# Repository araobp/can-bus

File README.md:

# IoT with CAN bus

Printed circuit design for CAN node

(I have not tested the printed circuit board yet, because I have been too busy in other priority works)

## Motivation

I want to develop very cheap and low power sensor/actuator network with electronic parts sold in [Akizuki-Denshi](http://akizukidenshi.com/catalog/default.aspx), Tokyo.

Most of parts I use are DIP.

## Architecture

### Basic concept

I pursue seamless communications between CAN-bus and MQTT-bus:

## Specification

The CAN node consists of one base board and one expansion board.

See this page for expansion boards: [EXPANSION BOARDS](./EXPANSION_BOARDS.md).

### CAN node base board

|Parameter           |Value                       |Note
|--------------------|----------------------------|---------------------------|
|PIC16F1 MCU clock   |32MHz(Internal OSC 8MHz * 4 PLL)                        |
|UART baud rate      |9600bps (fixed)             |Full-duplex wire-rate is not supported|
|SPI clock           |2MHz (fixed)                |                           |
|CAN speed           |Max. 250kHz (default 125kHz)|                           |
|Oscillator for CAN controller|8MHz (ceramic)     |Murata Ceralock            |
|Expansion board     |8 pins connected to PIC MCU |                           |

#### Circuit

#### PCB

#### BOM

|Part                      |Akizuki-denshi URL |Price in Yen |Quantity|
|--------------------------|-------------------|-------------|--------|
|Microchip PIC16F1825-I/P  |http://akizukidenshi.com/catalog/g/gI-10656/|150|1|
|Microchip PIC16F18326-I/P |http://akizukidenshi.com/catalog/g/gI-11886/|130|1|
|Microchip MCP2515         |http://akizukidenshi.com/catalog/g/gI-12030/|160|1|
|Microchip MCP2561         |http://akizukidenshi.com/catalog/g/gI-12483/|90|1|
|Murata Ceralock 8MHz      |http://akizukidenshi.com/catalog/g/gP-00153/|35|1|
|Regiter 51k ohm           |http://akizukidenshi.com/catalog/g/gR-25513/|1|1|
|Register 10k ohm          |http://akizukidenshi.com/catalog/g/gR-25103/|1|1|
|Register 120 ohm          |http://akizukidenshi.com/catalog/g/gR-25121/|1|1|
|Murata capacitor 0.1 micro F|http://akizukidenshi.com/catalog/g/gP-00090/|10|3|
|Diode 1A                  |http://akizukidenshi.com/catalog/g/gI-08332/|10|1|
|Toshiba TA48M05F (w/ capacitors)|http://akizukidenshi.com/catalog/g/gI-00451/|100|1|
|Polyswitch 250mA          |http://akizukidenshi.com/catalog/g/gP-01354|30|2|
|LED 3mm red               |http://akizukidenshi.com/catalog/g/gI-04780/|20|1|
|Tactile switch            |http://akizukidenshi.com/catalog/g/gP-08216/|20|1|
|IC sockets 14pins         |http://akizukidenshi.com/catalog/g/gP-00006/|10|1|
|IC sockets 18pins         |http://akizukidenshi.com/catalog/g/gP-00008/|10|1|
|IC sockets 8pins          |http://akizukidenshi.com/catalog/g/gP-00017/|10|1|
|Pin socket 6pins          |http://akizukidenshi.com/catalog/g/gC-03784/|20|1|
|Pin socket 4pins          |http://akizukidenshi.com/catalog/g/gC-10099/|20|2|
|Pin header L shape        |http://akizukidenshi.com/catalog/g/gC-01627/|50|1|
|Phenix Contact terminal block 2P|http://akizukidenshi.com/catalog/g/gP-08369/|20|1|

### CAN Standard Identifier format

This implementation supports CAN Standard Frame only (does not support Extended Frame). For home networking, 11bit Standard Identifier suffices.

=> [FORMAT](./doc/FORMAT.md)

### "CAN adapter to UART" command list

This implementation supports CAN adapter functionality for PC and Android.

```
/// UART2CAN HELP (version 0.11  March 19, 2018) ///
[Set standard identifier] @i<standard identifier>
[Set output mode] {debug: @vd, verbose: @vv, normal: @vn}
[Enable operation mode] {loopback: @ol, normal: @on}
     with SID: @ols or @ons
[Set mask] @m<n><mask(SID10 ~ SID0)>
[Set filter] @f<n><filter(SID10 ~ SID0)>
[Set baud rate] @b<bpr>
[Abort all pending transmissions] @a
[Dump masks and filters] @F
[Dump registers] @D
[Send message] <message>
[Send message beginning with '@' character] @<@message>
[Receive message] <message> will be output
[Show this help]: @h
```
For example, to receive messages with SID 5, 10 and 15, set masks and filters to the CAN adapter as follows:

```
@m02047  --> RXM0 0b11111111111
@f05     --> RXF0 0b00000000101 (SID 5 message to RXB0)
@f110    --> RXF1 0b00000001010 (SID 10 message to RXB0)
@m12047  --> RXM1 0b11111111111
@f215    --> RXF2 0b00000001111 (SID 15 message to RXB1)
```

---
## Development environment

- Microchip [MPLAB-X IDE](http://www.microchip.com/mplab/mplab-x-ide) with MCC plugin.
- [FreeCAD](https://www.freecadweb.org/)
- [KiCAD](http://kicad.org/)
- [3D printer BIQU Magician](https://www.biqu.equipment/collections/3d-printer/products/biqu-magician-3d-printer-new-diy-kit-mini-kossel-delta-printing)
- [RaspberryPi](https://www.raspberrypi.org/)

---

## Development plan and progress

### M1 (completed on March 17, 2018)

- Purchased CAN adaptors from Amazon.
- Evaluate CAN ==> [EVALUATION](./doc/EVALUATION.md).
- Developed my original ASCII-based protocol over serial for MCP2515. The protocol is mainly for evaluating MCP2515.

At first, I use [this universal board](http://akizukidenshi.com/catalog/g/gP-08241/) to make a prototype of the CAN adaptor:

I have finished the first prototype (Marth 25-27, 2018). I have made three boards, and it took eight hours.

### M2 (completed on April 1, 2018)

3D printed enclosure for CAN node

- Purchase three pairs of MCP2515 and MCP2561 in Akihabara.
- Develop my original CAN adaptor board.
- Develop [CAN-MQTT gateway](./gateway/gateway.js) on RasPi ~~and OpenWrt~~.
- Develop [a 3D-printed DIN rail enclosure](./cad/adapter_to_uart.stl) for the board by using [FreeCAD](https://www.freecadweb.org/).
- ~~Mount all of them on DIN rail (incl. RasPi).~~
- ~~Add [SLCAN](https://elixir.bootlin.com/linux/v3.4/source/drivers/net/can/slcan.c) that is ASCII-based protocol for SocketCAN.~~

### M3

- Evaluate [PIC16F18326](http://akizukidenshi.com/catalog/g/gI-11886/) that is cheaper than PIC16F1825 and supports two MSSPs.
- Use KiCAD to redesign the circuit for PIC16F18326.
- Adopt moduler architecture: base board and sensor/actuator building blocks.
- Support sensors and actuators: doppler sensor, CdS, servo motor etc.

---
## Reference

### Datasheet (Microchip/NXP/Murata)

#### Microchip
- [PIC16F1825](http://ww1.microchip.com/downloads/en/DeviceDoc/41440A.pdf)
- [MCP2515](http://ww1.microchip.com/downloads/en/DeviceDoc/21801d.pdf)
- [MCP2561](http://ww1.microchip.com/downloads/en/DeviceDoc/20005167C.pdf)
- [MCP2515DM-BM](http://www.microchip.com/Developmenttools/ProductDetails.aspx?PartNO=MCP2515DM-BM)

#### NXP
- [TJA1050](https://www.nxp.com/docs/en/data-sheet/TJA1050.pdf)

#### Murata
- [Ceralock](https://www.murata.com/~/media/webrenewal/support/library/catalog/products/timingdevice/ceralock/p17e.ashx)

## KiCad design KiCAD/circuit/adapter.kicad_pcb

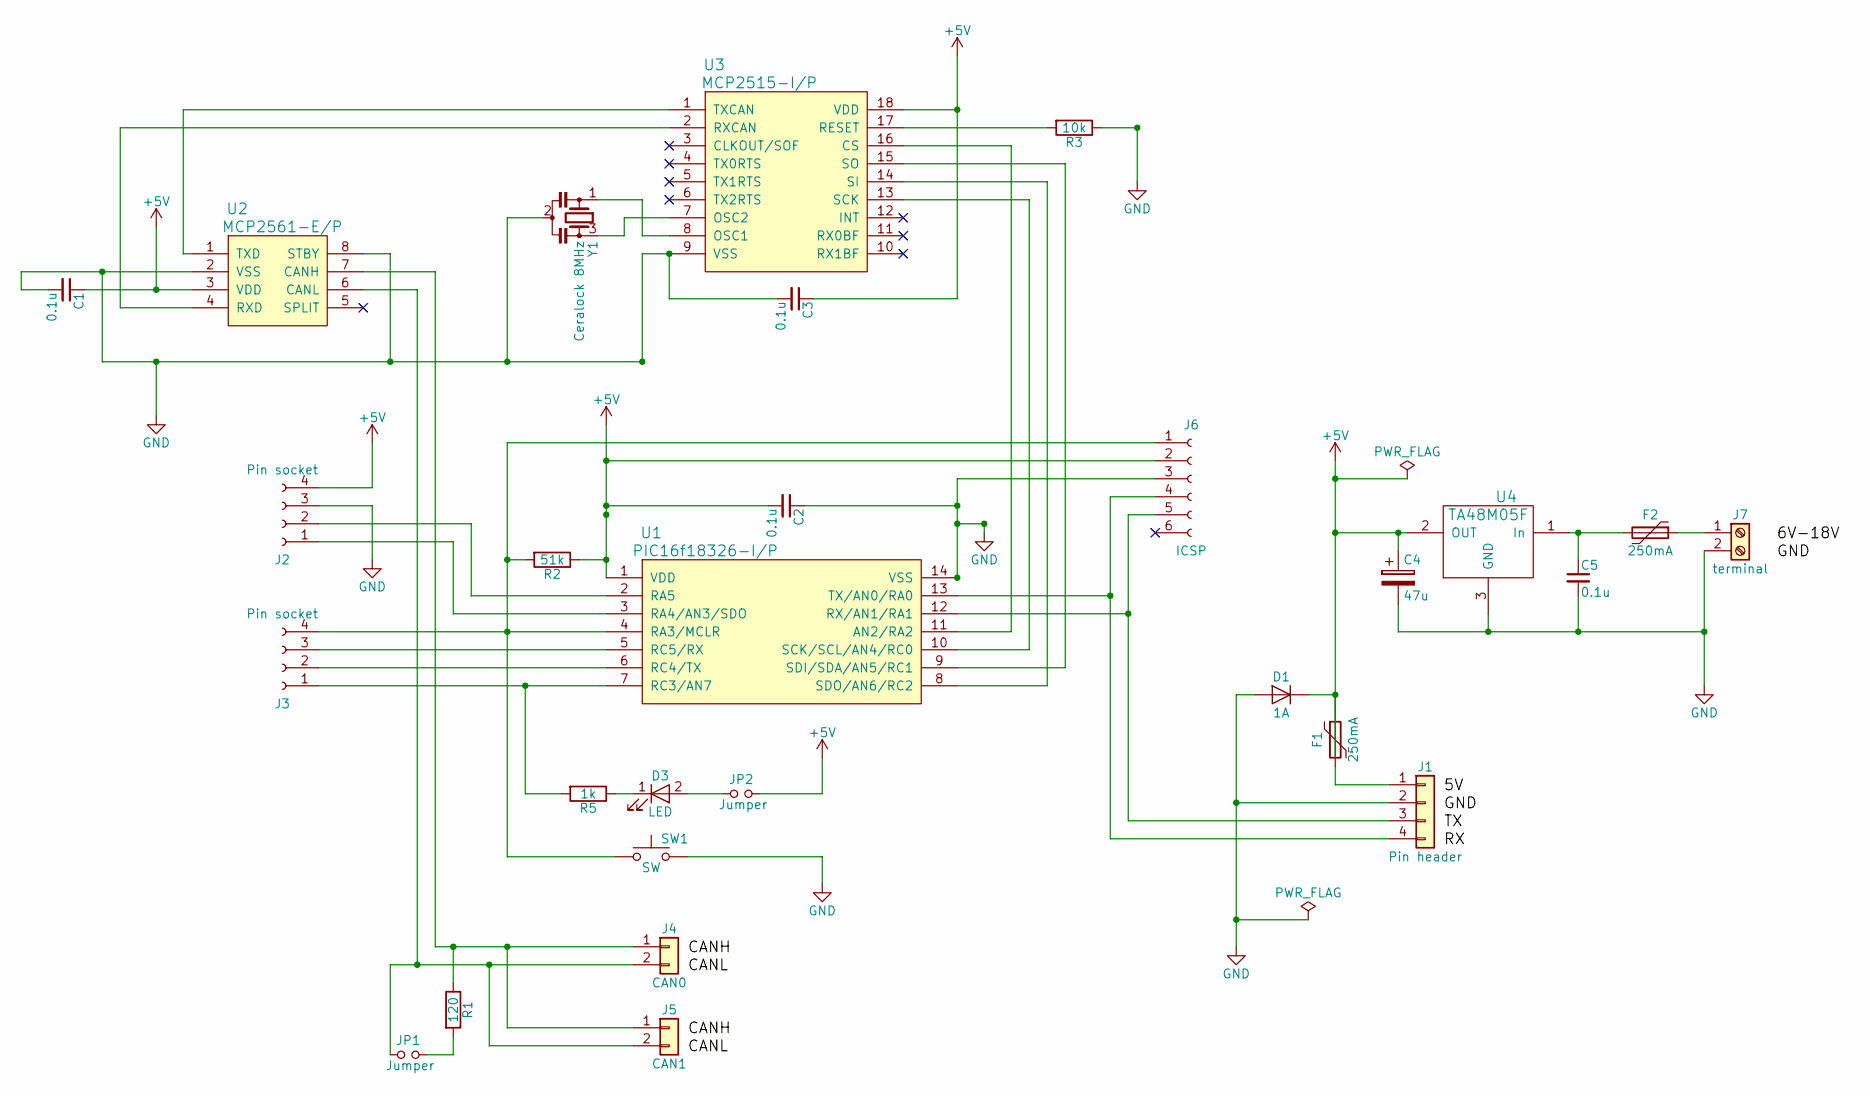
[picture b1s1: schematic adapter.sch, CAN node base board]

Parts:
C1, C2, C3, C5: 0.1u; Capacitor_2.54mm
C4: 47u; Capacitor_2.54mm
D1: 1A; Diode
D3: LED; Led
F1, F2: 250mA; Polyswitch_Tyco
J1: Pin header; PinHeader_1x4_L_Shape
J2, J3: Pin socket; PinSocket_1x4
J4: CAN0; PinHeader_1x2_L_Shape
J5: CAN1; PinHeader_1x2_L_Shape
J6: ICSP; PinSocket_1x6
J7: terminal; Terminal_PhoenixContact_2P
JP1, JP2: Jumper; Jumper_1x2
R1: 120; Resistor_FaithfulLink_CF25
R2: 51k; Resistor_FaithfulLink_CF25
R3: 10k; Resistor_FaithfulLink_CF25
R5: 1k; Resistor_FaithfulLink_CF25
SW1: SW; TactileSwitch
U1: PIC16f18326-I/P; IC_socket_14pins
U2: MCP2561-E/P; IC_Socket_8pins
U3: MCP2515-I/P; IC_socket_18pins
U4: TA48M05F
Y1: Ceralock 8MHz; Ceralock_Murata

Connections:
+5V: C1.1, C2.2, C3.1, C4.1, D1.1 (K), F1.1, J2.4, J6.2, JP2.2, R2.1, U1.1 (VDD), U2.3 (VDD), U3.18 (VDD), U4.2 (OUT)
GND: C1.2, C2.1, C3.2, C4.2, C5.2, D1.2 (A), J1.2, J2.3, J6.3, J7.2, R3.1, SW1.2, U1.14 (VSS), U2.2 (VSS), U2.8 (STBY), U3.9 (VSS), U4.3 (GND), Y1.2; also elsewhere on the board
unnamed: C5.1, F2.2, U4.1 (In)
unnamed: D3.1 (K), R5.1
unnamed: D3.2 (A), JP2.1
unnamed: F1.2, J1.1
unnamed: F2.1, J7.1
unnamed: J1.3, J6.5, U1.12 (RX/AN1/RA1)
unnamed: J1.4, J6.4, U1.13 (TX/AN0/RA0)
unnamed: J2.1, U1.3 (RA4/AN3/SDO)
unnamed: J2.2, U1.2 (RA5)
unnamed: J3.1, R5.2, U1.7 (RC3/AN7)
unnamed: J3.2, U1.6 (RC4/TX)
unnamed: J3.3, U1.5 (RC5/RX)
unnamed 14: J3.4, J6.1, R2.2, SW1.1, U1.4 (RA3/MCLR); also elsewhere on the board
unnamed: J4.1, J5.1, R1.1, U2.7 (CANH)
unnamed: J4.2, J5.2, JP1.1, U2.6 (CANL)
unnamed: JP1.2, R1.2
unnamed: R3.2, U3.17 (RESET)
unnamed: U1.8 (SDO/AN6/RC2), U3.14 (SI)
unnamed: U1.9 (SDI/SDA/AN5/RC1), U3.15 (SO)
unnamed: U1.10 (SCK/SCL/AN4/RC0), U3.13 (SCK)
unnamed: U1.11 (AN2/RA2), U3.16 (CS)
unnamed: U2.1 (TXD), U3.1 (TXCAN)
unnamed: U2.4 (RXD), U3.2 (RXCAN)
unnamed: U3.7 (OSC2), Y1.3
unnamed: U3.8 (OSC1), Y1.1

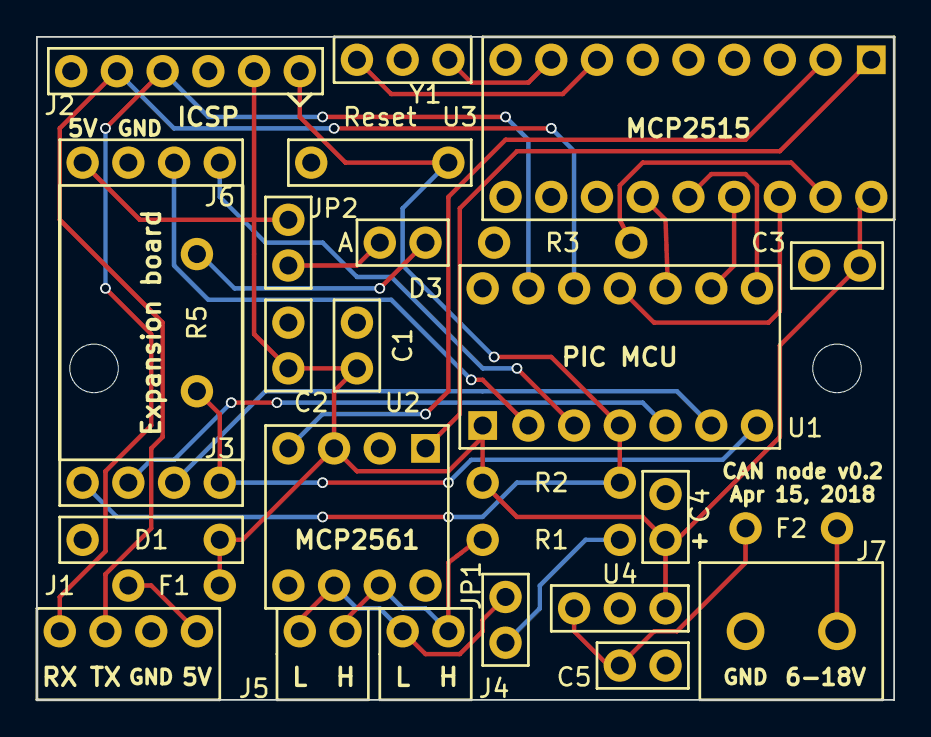
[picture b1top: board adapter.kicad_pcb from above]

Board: 2 copper layers, 47.6 x 36.8 mm, 28 parts (0 on the bottom side), 27 nets.

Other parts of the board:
Reset: SW; TactileSwitch

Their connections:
GND: Reset.2; also elsewhere on the board
unnamed 14: Reset.1; also elsewhere on the board

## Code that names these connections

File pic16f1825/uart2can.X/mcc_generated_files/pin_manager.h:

/**
  @Generated Pin Manager Header File

  @Company:
    Microchip Technology Inc.

  @File Name:
    pin_manager.h

  @Summary:
    This is the Pin Manager file generated using MPLAB(c) Code Configurator

  @Description:
    This header file provides implementations for pin APIs for all pins selected in the GUI.
    Generation Information :
        Product Revision  :  MPLAB(c) Code Configurator - 4.35
        Device            :  PIC16F1825
        Version           :  1.01
    The generated drivers are tested against the following:
        Compiler          :  XC8 1.35
        MPLAB             :  MPLAB X 3.40

    Copyright (c) 2013 - 2015 released Microchip Technology Inc.  All rights reserved.

    Microchip licenses to you the right to use, modify, copy and distribute
    Software only when embedded on a Microchip microcontroller or digital signal
    controller that is integrated into your product or third party product
    (pursuant to the sublicense terms in the accompanying license agreement).

    You should refer to the license agreement accompanying this Software for
    additional information regarding your rights and obligations.

    SOFTWARE AND DOCUMENTATION ARE PROVIDED "AS IS" WITHOUT WARRANTY OF ANY KIND,
    EITHER EXPRESS OR IMPLIED, INCLUDING WITHOUT LIMITATION, ANY WARRANTY OF
    MERCHANTABILITY, TITLE, NON-INFRINGEMENT AND FITNESS FOR A PARTICULAR PURPOSE.
    IN NO EVENT SHALL MICROCHIP OR ITS LICENSORS BE LIABLE OR OBLIGATED UNDER
    CONTRACT, NEGLIGENCE, STRICT LIABILITY, CONTRIBUTION, BREACH OF WARRANTY, OR
    OTHER LEGAL EQUITABLE THEORY ANY DIRECT OR INDIRECT DAMAGES OR EXPENSES
    INCLUDING BUT NOT LIMITED TO ANY INCIDENTAL, SPECIAL, INDIRECT, PUNITIVE OR
    CONSEQUENTIAL DAMAGES, LOST PROFITS OR LOST DATA, COST OF PROCUREMENT OF
    SUBSTITUTE GOODS, TECHNOLOGY, SERVICES, OR ANY CLAIMS BY THIRD PARTIES
    (INCLUDING BUT NOT LIMITED TO ANY DEFENSE THEREOF), OR OTHER SIMILAR COSTS.

*/


#ifndef PIN_MANAGER_H
#define PIN_MANAGER_H

#define INPUT   1
#define OUTPUT  0

#define HIGH    1
#define LOW     0

#define ANALOG      1
#define DIGITAL     0

#define PULL_UP_ENABLED      1
#define PULL_UP_DISABLED     0

// get/set RA0 procedures
#define RA0_SetHigh()    do { LATAbits.LATA0 = 1; } while(0)
#define RA0_SetLow()   do { LATAbits.LATA0 = 0; } while(0)
#define RA0_Toggle()   do { LATAbits.LATA0 = ~LATAbits.LATA0; } while(0)
#define RA0_GetValue()         PORTAbits.RA0
#define RA0_SetDigitalInput()   do { TRISAbits.TRISA0 = 1; } while(0)
#define RA0_SetDigitalOutput()  do { TRISAbits.TRISA0 = 0; } while(0)
#define RA0_SetPullup()     do { WPUAbits.WPUA0 = 1; } while(0)
#define RA0_ResetPullup()   do { WPUAbits.WPUA0 = 0; } while(0)
#define RA0_SetAnalogMode() do { ANSELAbits.ANSA0 = 1; } while(0)
#define RA0_SetDigitalMode()do { ANSELAbits.ANSA0 = 0; } while(0)

// get/set RA1 procedures
#define RA1_SetHigh()    do { LATAbits.LATA1 = 1; } while(0)
#define RA1_SetLow()   do { LATAbits.LATA1 = 0; } while(0)
#define RA1_Toggle()   do { LATAbits.LATA1 = ~LATAbits.LATA1; } while(0)
#define RA1_GetValue()         PORTAbits.RA1
#define RA1_SetDigitalInput()   do { TRISAbits.TRISA1 = 1; } while(0)
#define RA1_SetDigitalOutput()  do { TRISAbits.TRISA1 = 0; } while(0)
#define RA1_SetPullup()     do { WPUAbits.WPUA1 = 1; } while(0)
#define RA1_ResetPullup()   do { WPUAbits.WPUA1 = 0; } while(0)
#define RA1_SetAnalogMode() do { ANSELAbits.ANSA1 = 1; } while(0)
#define RA1_SetDigitalMode()do { ANSELAbits.ANSA1 = 0; } while(0)

// get/set IO_RA2 aliases
#define IO_RA2_TRIS               TRISAbits.TRISA2
#define IO_RA2_LAT                LATAbits.LATA2
#define IO_RA2_PORT               PORTAbits.RA2
#define IO_RA2_WPU                WPUAbits.WPUA2
#define IO_RA2_ANS                ANSELAbits.ANSA2
#define IO_RA2_SetHigh()            do { LATAbits.LATA2 = 1; } while(0)
#define IO_RA2_SetLow()             do { LATAbits.LATA2 = 0; } while(0)
#define IO_RA2_Toggle()             do { LATAbits.LATA2 = ~LATAbits.LATA2; } while(0)
#define IO_RA2_GetValue()           PORTAbits.RA2
#define IO_RA2_SetDigitalInput()    do { TRISAbits.TRISA2 = 1; } while(0)
#define IO_RA2_SetDigitalOutput()   do { TRISAbits.TRISA2 = 0; } while(0)
#define IO_RA2_SetPullup()      do { WPUAbits.WPUA2 = 1; } while(0)
#define IO_RA2_ResetPullup()    do { WPUAbits.WPUA2 = 0; } while(0)
#define IO_RA2_SetAnalogMode()  do { ANSELAbits.ANSA2 = 1; } while(0)
#define IO_RA2_SetDigitalMode() do { ANSELAbits.ANSA2 = 0; } while(0)

// get/set SCK aliases
#define SCK_TRIS               TRISCbits.TRISC0
#define SCK_LAT                LATCbits.LATC0
#define SCK_PORT               PORTCbits.RC0
#define SCK_WPU                WPUCbits.WPUC0
#define SCK_ANS                ANSELCbits.ANSC0
#define SCK_SetHigh()            do { LATCbits.LATC0 = 1; } while(0)
#define SCK_SetLow()             do { LATCbits.LATC0 = 0; } while(0)
#define SCK_Toggle()             do { LATCbits.LATC0 = ~LATCbits.LATC0; } while(0)
#define SCK_GetValue()           PORTCbits.RC0
#define SCK_SetDigitalInput()    do { TRISCbits.TRISC0 = 1; } while(0)
#define SCK_SetDigitalOutput()   do { TRISCbits.TRISC0 = 0; } while(0)
#define SCK_SetPullup()      do { WPUCbits.WPUC0 = 1; } while(0)
#define SCK_ResetPullup()    do { WPUCbits.WPUC0 = 0; } while(0)
#define SCK_SetAnalogMode()  do { ANSELCbits.ANSC0 = 1; } while(0)
#define SCK_SetDigitalMode() do { ANSELCbits.ANSC0 = 0; } while(0)

// get/set SDI aliases
#define SDI_TRIS               TRISCbits.TRISC1
#define SDI_LAT                LATCbits.LATC1
#define SDI_PORT               PORTCbits.RC1
#define SDI_WPU                WPUCbits.WPUC1
#define SDI_ANS                ANSELCbits.ANSC1
#define SDI_SetHigh()            do { LATCbits.LATC1 = 1; } while(0)
#define SDI_SetLow()             do { LATCbits.LATC1 = 0; } while(0)
#define SDI_Toggle()             do { LATCbits.LATC1 = ~LATCbits.LATC1; } while(0)
#define SDI_GetValue()           PORTCbits.RC1
#define SDI_SetDigitalInput()    do { TRISCbits.TRISC1 = 1; } while(0)
#define SDI_SetDigitalOutput()   do { TRISCbits.TRISC1 = 0; } while(0)
#define SDI_SetPullup()      do { WPUCbits.WPUC1 = 1; } while(0)
#define SDI_ResetPullup()    do { WPUCbits.WPUC1 = 0; } while(0)
#define SDI_SetAnalogMode()  do { ANSELCbits.ANSC1 = 1; } while(0)
#define SDI_SetDigitalMode() do { ANSELCbits.ANSC1 = 0; } while(0)

// get/set SDO aliases
#define SDO_TRIS               TRISCbits.TRISC2
#define SDO_LAT                LATCbits.LATC2
#define SDO_PORT               PORTCbits.RC2
#define SDO_WPU                WPUCbits.WPUC2
#define SDO_ANS                ANSELCbits.ANSC2
#define SDO_SetHigh()            do { LATCbits.LATC2 = 1; } while(0)
#define SDO_SetLow()             do { LATCbits.LATC2 = 0; } while(0)
#define SDO_Toggle()             do { LATCbits.LATC2 = ~LATCbits.LATC2; } while(0)
#define SDO_GetValue()           PORTCbits.RC2
#define SDO_SetDigitalInput()    do { TRISCbits.TRISC2 = 1; } while(0)
#define SDO_SetDigitalOutput()   do { TRISCbits.TRISC2 = 0; } while(0)
#define SDO_SetPullup()      do { WPUCbits.WPUC2 = 1; } while(0)
#define SDO_ResetPullup()    do { WPUCbits.WPUC2 = 0; } while(0)
#define SDO_SetAnalogMode()  do { ANSELCbits.ANSC2 = 1; } while(0)
#define SDO_SetDigitalMode() do { ANSELCbits.ANSC2 = 0; } while(0)

// get/set IO_RC3 aliases
#define IO_RC3_TRIS               TRISCbits.TRISC3
#define IO_RC3_LAT                LATCbits.LATC3
#define IO_RC3_PORT               PORTCbits.RC3
#define IO_RC3_WPU                WPUCbits.WPUC3
#define IO_RC3_ANS                ANSELCbits.ANSC3
#define IO_RC3_SetHigh()            do { LATCbits.LATC3 = 1; } while(0)
#define IO_RC3_SetLow()             do { LATCbits.LATC3 = 0; } while(0)
#define IO_RC3_Toggle()             do { LATCbits.LATC3 = ~LATCbits.LATC3; } while(0)
#define IO_RC3_GetValue()           PORTCbits.RC3
#define IO_RC3_SetDigitalInput()    do { TRISCbits.TRISC3 = 1; } while(0)
#define IO_RC3_SetDigitalOutput()   do { TRISCbits.TRISC3 = 0; } while(0)
#define IO_RC3_SetPullup()      do { WPUCbits.WPUC3 = 1; } while(0)
#define IO_RC3_ResetPullup()    do { WPUCbits.WPUC3 = 0; } while(0)
#define IO_RC3_SetAnalogMode()  do { ANSELCbits.ANSC3 = 1; } while(0)
#define IO_RC3_SetDigitalMode() do { ANSELCbits.ANSC3 = 0; } while(0)

/**
   @Param
    none
   @Returns
    none
   @Description
    GPIO and peripheral I/O initialization
   @Example
    PIN_MANAGER_Initialize();
 */
void PIN_MANAGER_Initialize (void);

/**
 * @Param
    none
 * @Returns
    none
 * @Description
    Interrupt on Change Handling routine
 * @Example
    PIN_MANAGER_IOC();
 */
void PIN_MANAGER_IOC(void);



#endif // PIN_MANAGER_H
/**
 End of File
*/

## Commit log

2018-03-10 command
2018-03-11 update
    Add SPI write routine
2018-03-13 basic functionality completed
2018-03-13 waveform
2018-03-13 test
2018-03-13 command update
2018-03-14 CNF1 to CNF3 config
2018-03-15 modulerize
2018-03-16 Version 0.1 (March 18, 2018)
    Version 0.1 release
2018-03-16 Create LICENSE
2018-03-17 bug fix
    CNF1 not initialized correctly
2018-03-17 capture
2018-03-17 universal board
2018-03-18 logic_analyzer
2018-03-18 osc001
2018-03-22 SLCAN support (partly)
2018-03-22 SLCAN support
2018-03-23 Remove SLCAN support
2018-03-24 pic update
2018-03-24 circuit update
2018-03-25 README update
2018-03-26 clock speed 32MHz
    2MHz is too slow to receive data from UART.
2018-03-26 bug fix
2018-03-26 test.js
2018-03-27 daisy chain
2018-03-28 console
2018-03-30 Format drafting
2018-03-30 gateway script
2018-03-30 gateway script update
2018-03-30 concept picture
2018-03-31 3D cad data
2018-03-31 3D CAD data update
2018-04-01 cad data update
2018-04-01 3d_printed
2018-04-03 KiCAD folder
2018-04-03 circuit
2018-04-03 cad to FreeCAD
2018-04-04 KiCAD data update
2018-04-15 add pic
2018-04-18 add thermistor project
